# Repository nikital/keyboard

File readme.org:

#+STARTUP: indent

* Layout
Generated at http://www.keyboard-layout-editor.com/

* Plate
Generated at http://builder.swillkb.com/
- Switch Type: MX
- Stabilizer: Cherry Only

* PCB

** Placement
5.7mm 7.5mm For diodes from pin 1

** Components

*** MCU
ATMEGA32U4-AU

*** PPTC
MF-PSMF020X-2

*** I/O expander
MCP23018-E/SO

*** Resistors (2012/0805)

*** ESD protection
PRTR5V0U2X

* Burn
Load DFU bootloader. When using Arduino as ISP, first burn an Arduino using the
ArduinoISP example sketch. Then wire everything according to comments. Make sure
to use a good 5V source and the the 5V on ICSP (not sure why, but it glitched).
Then run:
#+begin_src sh
avrdude -patmega32u4 -cstk500v1 -P/dev/ttyUSB0 -b19200 -e -U flash:w:dfu/ATMega32U4-usbdevice_dfu-1_0_0.hex:i -U lfuse:w:0b01011110:m -U hfuse:w:0b10011001:m -U efuse:w:0b11000011:m -U lock:w:0b101100:m
#+end_src

If using a USBasp based programmer, use: =-cusbasp=.
#+begin_src sh
avrdude -patmega32u4 -cusbasp -e -U flash:w:dfu/ATMega32U4-usbdevice_dfu-1_0_0.hex:i -U lfuse:w:0b01011110:m -U hfuse:w:0b10011001:m -U efuse:w:0b11000011:m -U lock:w:0b101100:m
#+end_src

Make sure to issue an ~dfu-programmer atmega32u4 erase --force~ to make sure that the flash
is writable.

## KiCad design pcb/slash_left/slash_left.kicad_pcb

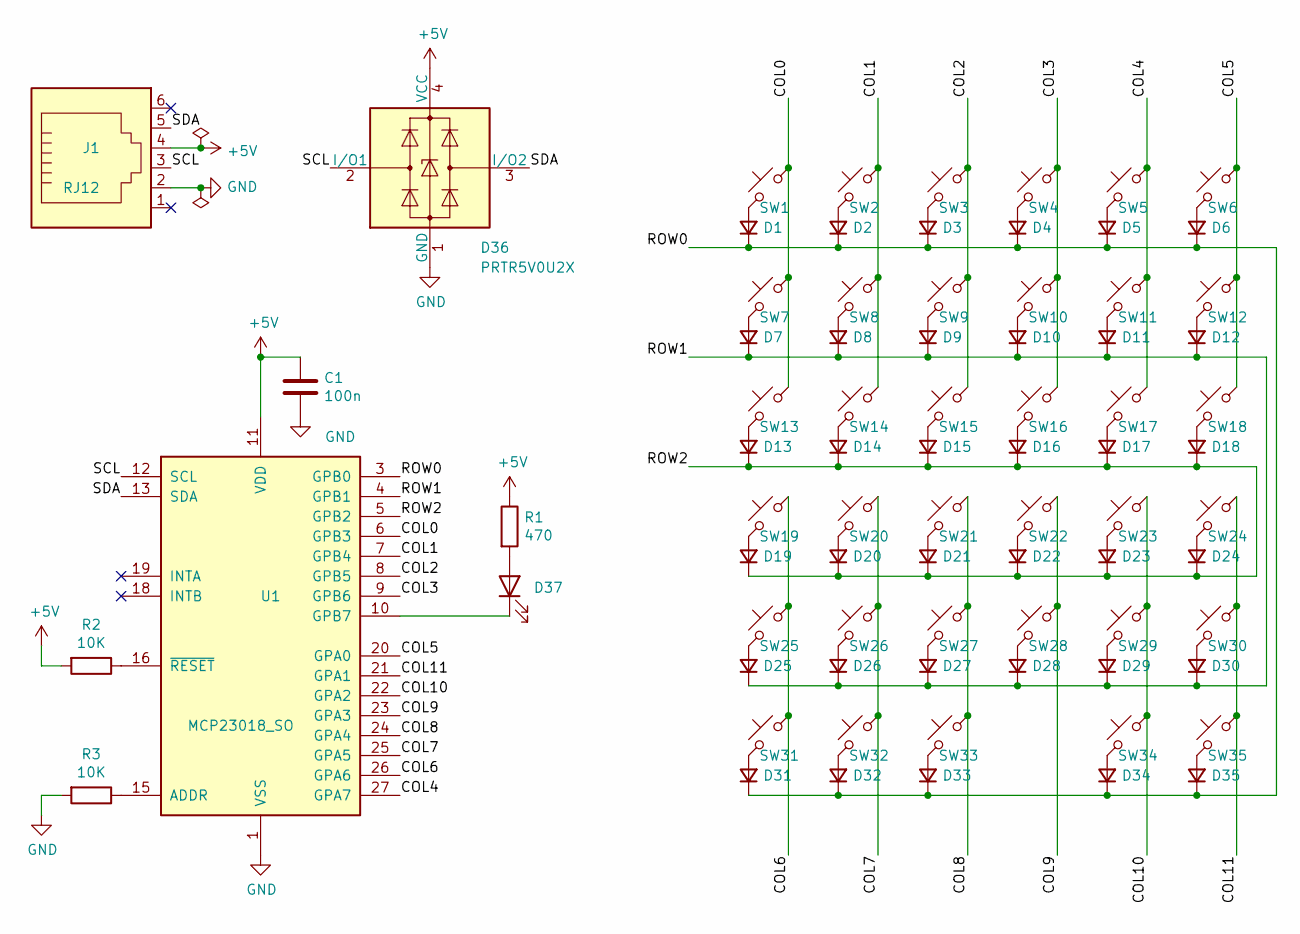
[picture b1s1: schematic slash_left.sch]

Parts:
C1: 100n; C_0805_2012Metric_Pad1.18x1.45mm_HandSolder
D1, D2, D3, D4, D5, D6, D7, D8, D9, D10, D11, D12, D13, D14, D15, D16, D17, D18, D19, D20, D21, D22, D23, D24, D25, D26, D27, D28, D29, D30, D31, D32, D33, D34, D35: D_Small; D_SOD-123
D36: PRTR5V0U2X; SOT-143
D37: LED; LED_0805_2012Metric_Pad1.15x1.40mm_HandSolder
J1: RJ12; RJ12_Custom1
R1: 470; R_0805_2012Metric_Pad1.20x1.40mm_HandSolder
R2, R3: 10K; R_0805_2012Metric_Pad1.20x1.40mm_HandSolder
SW1, SW2, SW3, SW4, SW5, SW6, SW7, SW8, SW9, SW10, SW11, SW12, SW13, SW14, SW15, SW16, SW17, SW18, SW19, SW20, SW21, SW22, SW23, SW24, SW25, SW26, SW27, SW28, SW29, SW30, SW31, SW32, SW33, SW34, SW35: SW_Push_45deg; Kailh_socket_MX
U1: MCP23018_SO; SOIC-28W_7.5x17.9mm_P1.27mm

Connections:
+5V: C1.1, D36.4 (VCC), J1.4, R1.1, R2.2, U1.11 (VDD)
/COL0: SW1.2, SW7.2, SW13.2, U1.6 (GPB3)
/COL1: SW2.2, SW8.2, SW14.2, U1.7 (GPB4)
/COL2: SW3.2, SW9.2, SW15.2, U1.8 (GPB5)
/COL3: SW4.2, SW10.2, SW16.2, U1.9 (GPB6)
/COL4: SW5.2, SW11.2, SW17.2, U1.27 (GPA7)
/COL5: SW6.2, SW12.2, SW18.2, U1.20 (GPA0)
/COL6: SW19.2, SW25.2, SW31.2, U1.26 (GPA6)
/COL7: SW20.2, SW26.2, SW32.2, U1.25 (GPA5)
/COL8: SW21.2, SW27.2, SW33.2, U1.24 (GPA4)
/COL9: SW22.2, SW28.2, U1.23 (GPA3)
/COL10: SW23.2, SW29.2, SW34.2, U1.22 (GPA2)
/COL11: SW24.2, SW30.2, SW35.2, U1.21 (GPA1)
/ROW0: D1.1 (K), D2.1 (K), D3.1 (K), D4.1 (K), D5.1 (K), D6.1 (K), D31.1 (K), D32.1 (K), D33.1 (K), D34.1 (K), D35.1 (K), U1.3 (GPB0)
/ROW1: D7.1 (K), D8.1 (K), D9.1 (K), D10.1 (K), D11.1 (K), D12.1 (K), D25.1 (K), D26.1 (K), D27.1 (K), D28.1 (K), D29.1 (K), D30.1 (K), U1.4 (GPB1)
/ROW2: D13.1 (K), D14.1 (K), D15.1 (K), D16.1 (K), D17.1 (K), D18.1 (K), D19.1 (K), D20.1 (K), D21.1 (K), D22.1 (K), D23.1 (K), D24.1 (K), U1.5 (GPB2)
/SCL: D36.2 (I/O1), J1.3, U1.12 (SCL)
/SDA: D36.3 (I/O2), J1.5, U1.13 (SDA)
GND: C1.2, D36.1 (GND), J1.2, R3.2, U1.1 (VSS)
unnamed: D1.2 (A), SW1.1
unnamed: D2.2 (A), SW2.1
unnamed: D3.2 (A), SW3.1
unnamed: D4.2 (A), SW4.1
unnamed: D5.2 (A), SW5.1
unnamed: D6.2 (A), SW6.1
unnamed: D7.2 (A), SW7.1
unnamed: D8.2 (A), SW8.1
unnamed: D9.2 (A), SW9.1
unnamed: D10.2 (A), SW10.1
unnamed: D11.2 (A), SW11.1
unnamed: D12.2 (A), SW12.1
unnamed: D13.2 (A), SW13.1
unnamed: D14.2 (A), SW14.1
unnamed: D15.2 (A), SW15.1
unnamed: D16.2 (A), SW16.1
unnamed: D17.2 (A), SW17.1
unnamed: D18.2 (A), SW18.1
unnamed: D19.2 (A), SW19.1
unnamed: D20.2 (A), SW20.1
unnamed: D21.2 (A), SW21.1
unnamed: D22.2 (A), SW22.1
unnamed: D23.2 (A), SW23.1
unnamed: D24.2 (A), SW24.1
unnamed: D25.2 (A), SW25.1
unnamed: D26.2 (A), SW26.1
unnamed: D27.2 (A), SW27.1
unnamed: D28.2 (A), SW28.1
unnamed: D29.2 (A), SW29.1
unnamed: D30.2 (A), SW30.1
unnamed: D31.2 (A), SW31.1
unnamed: D32.2 (A), SW32.1
unnamed: D33.2 (A), SW33.1
unnamed: D34.2 (A), SW34.1
unnamed: D35.2 (A), SW35.1
unnamed: D37.1 (K), U1.10 (GPB7)
unnamed: D37.2 (A), R1.2
unnamed: R2.1, U1.16 (~RESET)
unnamed: R3.1, U1.15 (ADDR)

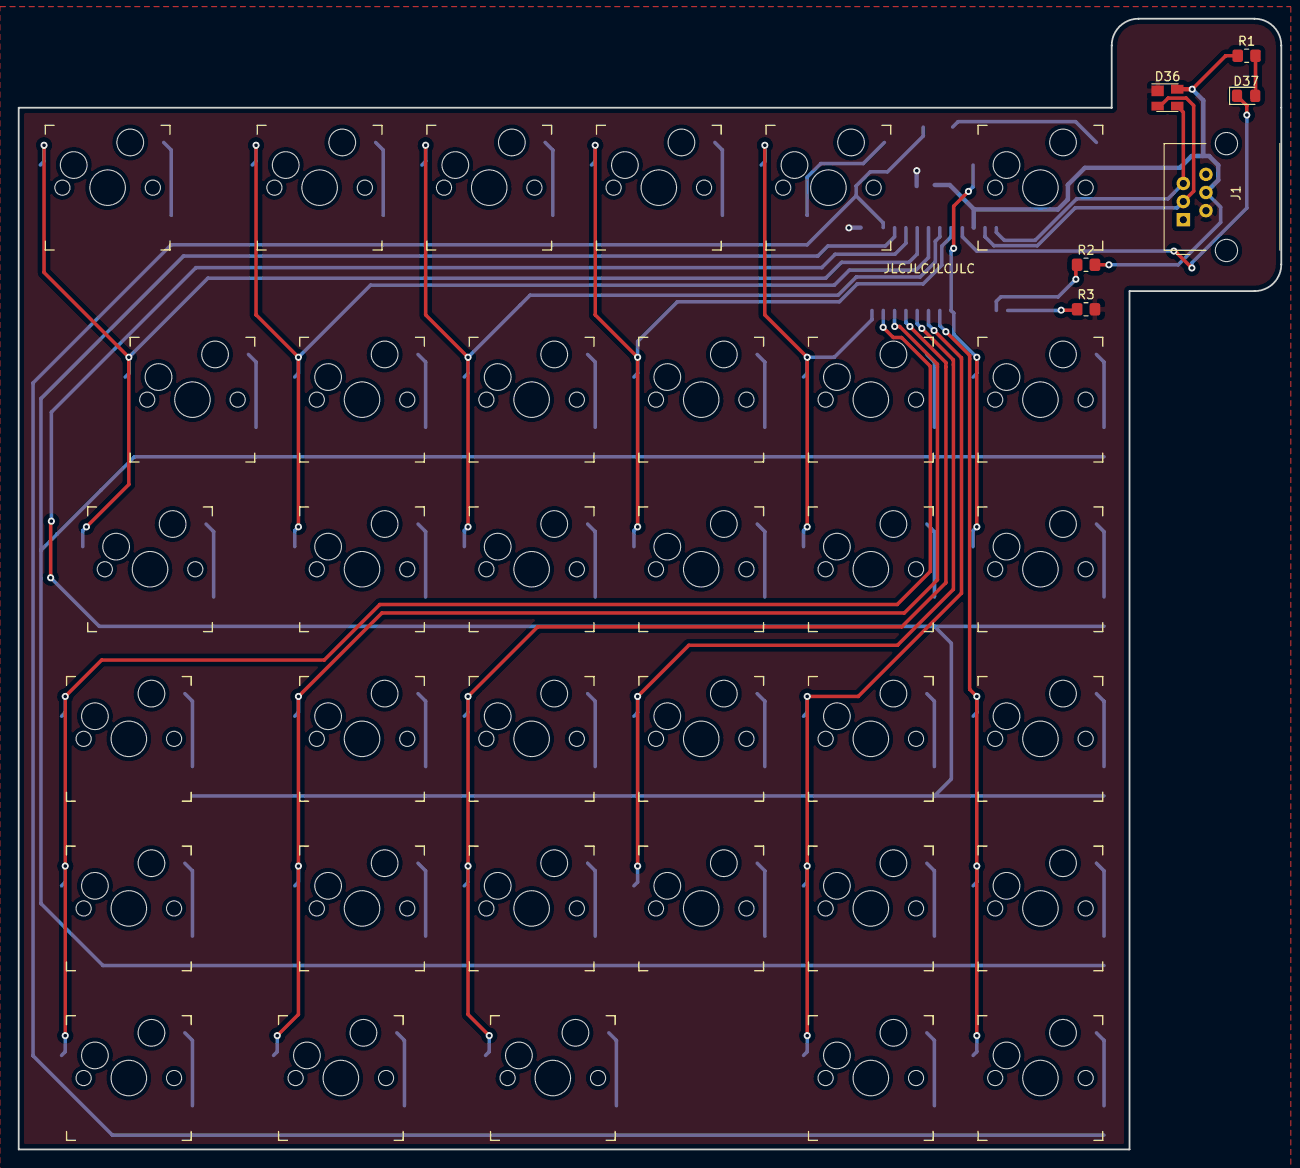
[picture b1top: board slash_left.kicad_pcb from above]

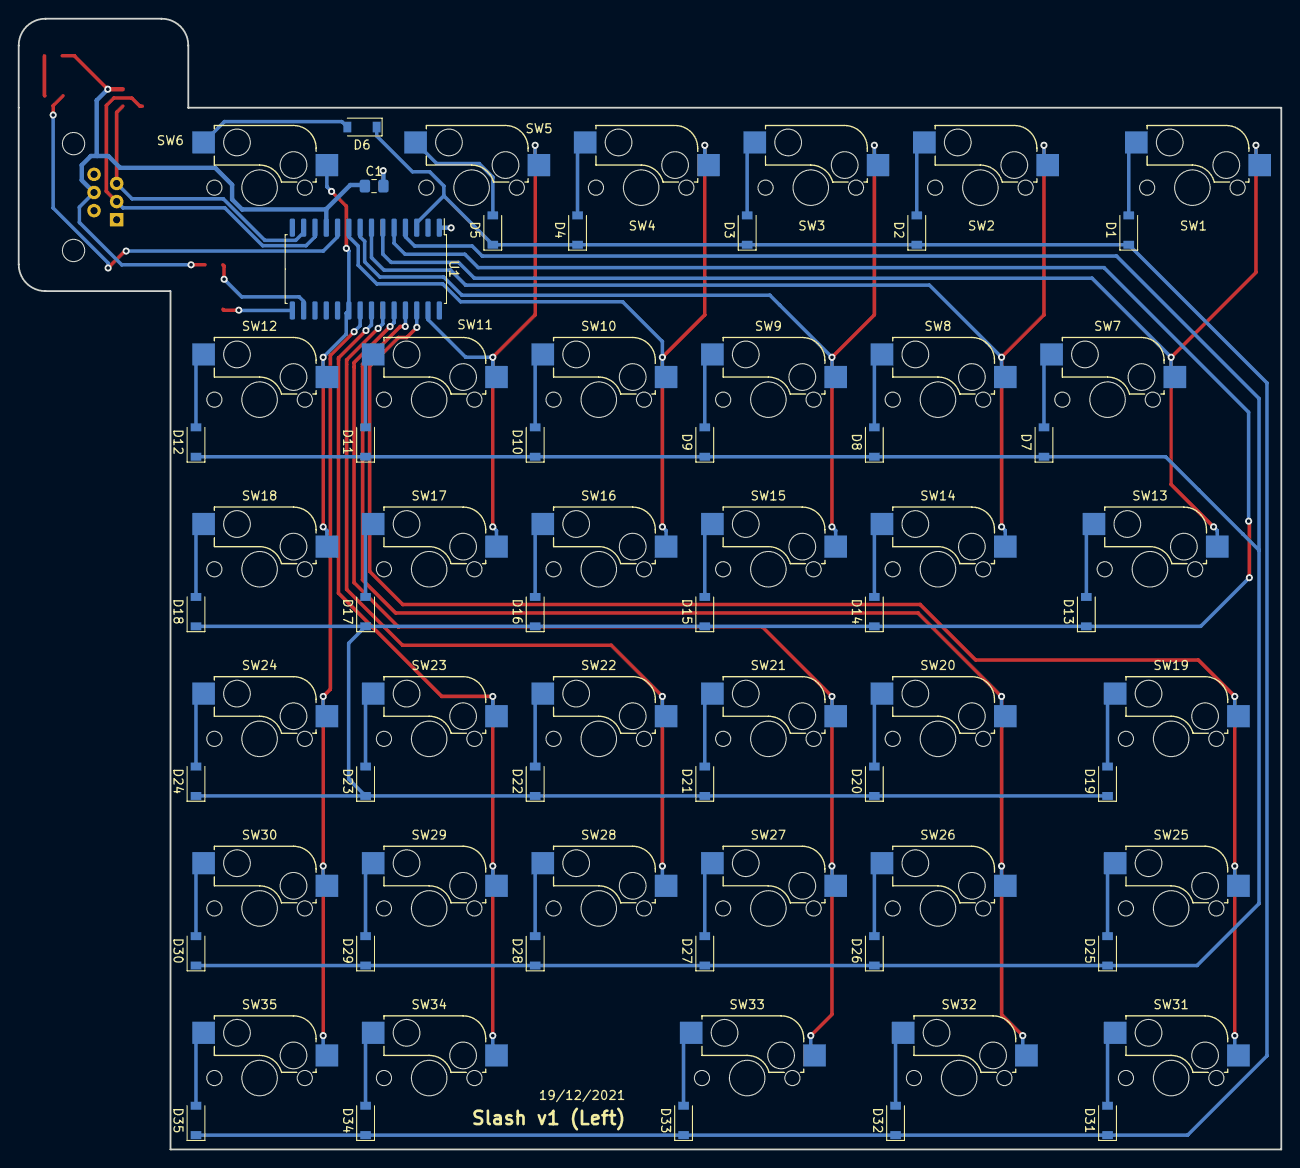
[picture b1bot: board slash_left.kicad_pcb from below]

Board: 2 copper layers, 141.8 x 127.0 mm, 78 parts (37 on the bottom side), 58 nets.

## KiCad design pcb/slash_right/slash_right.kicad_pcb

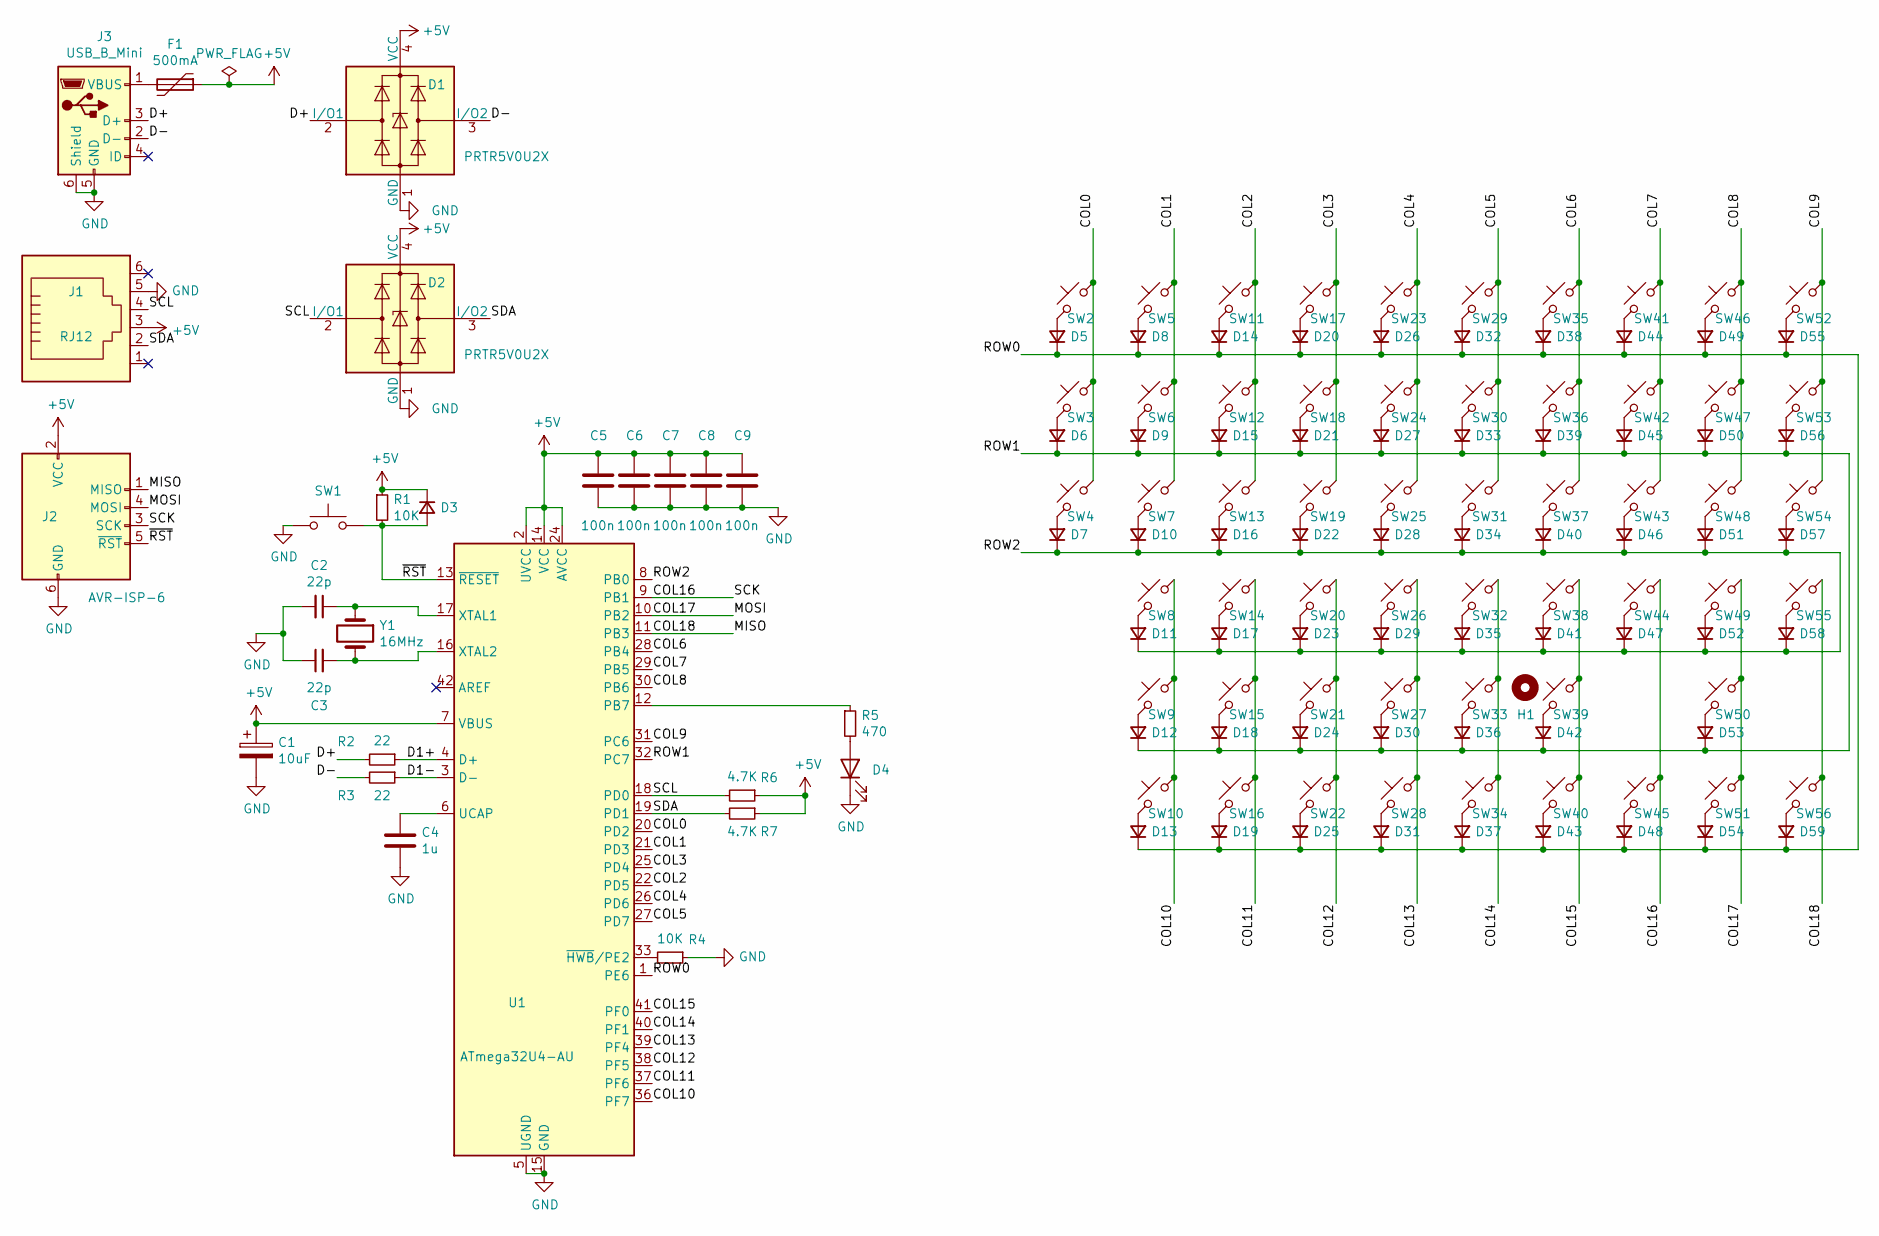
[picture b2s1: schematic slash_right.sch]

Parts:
C1: 10uF; CP_EIA-3216-18_Kemet-A_Pad1.58x1.35mm_HandSolder
C2, C3: 22p; C_0805_2012Metric_Pad1.18x1.45mm_HandSolder
C4: 1u; C_0805_2012Metric_Pad1.18x1.45mm_HandSolder
C5, C6, C7, C8, C9: 100n; C_0805_2012Metric_Pad1.18x1.45mm_HandSolder
D1, D2: PRTR5V0U2X; SOT-143
D3, D5, D6, D7, D8, D9, D10, D11, D12, D13, D14, D15, D16, D17, D18, D19, D20, D21, D22, D23, D24, D25, D26, D27, D28, D29, D30, D31, D32, D33, D34, D35, D36, D37, D38, D39, D40, D41, D42, D43, D44, D45, D46, D47, D48, D49, D50, D51, D52, D53, D54, D55, D56, D57, D58, D59: D_Small; D_SOD-123
D4: LED; LED_0805_2012Metric_Pad1.15x1.40mm_HandSolder
F1: 500mA; Fuse_0805_2012Metric_Pad1.15x1.40mm_HandSolder
H1: MountingHole; Stabilizer_MX_2u
J1: RJ12; RJ12_Custom1
J2: AVR-ISP-6; PinHeader_2x03_P2.54mm_Vertical
J3: USB_B_Mini; USB_Mini-B_Custom1_Horizontal
R1, R4: 10K; R_0805_2012Metric_Pad1.20x1.40mm_HandSolder
R2, R3: 22; R_0805_2012Metric_Pad1.20x1.40mm_HandSolder
R5: 470; R_0805_2012Metric_Pad1.20x1.40mm_HandSolder
R6, R7: 4.7K; R_0805_2012Metric_Pad1.20x1.40mm_HandSolder
SW1: SW_Push; SW_PUSH_6mm_H4.3mm
SW2, SW3, SW4, SW5, SW6, SW7, SW8, SW9, SW10, SW11, SW12, SW13, SW14, SW15, SW16, SW17, SW18, SW19, SW20, SW21, SW22, SW23, SW24, SW25, SW26, SW27, SW28, SW29, SW30, SW31, SW32, SW33, SW34, SW35, SW36, SW37, SW38, SW39, SW40, SW41, SW42, SW43, SW44, SW45, SW46, SW47, SW48, SW49, SW50, SW51, SW52, SW53, SW54, SW55, SW56: SW_Push_45deg; Kailh_socket_MX
U1: ATmega32U4-AU; TQFP-44_10x10mm_P0.8mm
Y1: 16MHz; Crystal_HC49-U_Vertical

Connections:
+5V: C1.1, C5.1, C6.1, C7.1, C8.1, C9.1, D1.4 (VCC), D2.4 (VCC), D3.1 (K), F1.1, J1.3, J2.2 (VCC), R1.1, R6.1, R7.1, U1.2 (UVCC), U1.7 (VBUS), U1.14 (VCC), U1.24 (AVCC), U1.34 (VCC), U1.44 (AVCC)
/COL0: SW2.2, SW3.2, SW4.2, U1.20 (PD2)
/COL1: SW5.2, SW6.2, SW7.2, U1.21 (PD3)
/COL2: SW11.2, SW12.2, SW13.2, U1.22 (PD5)
/COL3: SW17.2, SW18.2, SW19.2, U1.25 (PD4)
/COL4: SW23.2, SW24.2, SW25.2, U1.26 (PD6)
/COL5: SW29.2, SW30.2, SW31.2, U1.27 (PD7)
/COL6: SW35.2, SW36.2, SW37.2, U1.28 (PB4)
/COL7: SW41.2, SW42.2, SW43.2, U1.29 (PB5)
/COL8: SW46.2, SW47.2, SW48.2, U1.30 (PB6)
/COL9: SW52.2, SW53.2, SW54.2, U1.31 (PC6)
/COL10: SW8.2, SW9.2, SW10.2, U1.36 (PF7)
/COL11: SW14.2, SW15.2, SW16.2, U1.37 (PF6)
/COL12: SW20.2, SW21.2, SW22.2, U1.38 (PF5)
/COL13: SW26.2, SW27.2, SW28.2, U1.39 (PF4)
/COL14: SW32.2, SW33.2, SW34.2, U1.40 (PF1)
/COL15: SW38.2, SW39.2, SW40.2, U1.41 (PF0)
/COL16: J2.3 (SCK), SW44.2, SW45.2, U1.9 (PB1)
/COL17: J2.4 (MOSI), SW49.2, SW50.2, SW51.2, U1.10 (PB2)
/COL18: J2.1 (MISO), SW55.2, SW56.2, U1.11 (PB3)
/D1+: R2.1, U1.4 (D+)
/D1-: R3.1, U1.3 (D-)
/D+: D1.2 (I/O1), J3.3 (D+), R2.2
/D-: D1.3 (I/O2), J3.2 (D-), R3.2
/ROW0: D5.1 (K), D8.1 (K), D13.1 (K), D14.1 (K), D19.1 (K), D20.1 (K), D25.1 (K), D26.1 (K), D31.1 (K), D32.1 (K), D37.1 (K), D38.1 (K), D43.1 (K), D44.1 (K), D48.1 (K), D49.1 (K), D54.1 (K), D55.1 (K), D59.1 (K), U1.1 (PE6)
/ROW1: D6.1 (K), D9.1 (K), D12.1 (K), D15.1 (K), D18.1 (K), D21.1 (K), D24.1 (K), D27.1 (K), D30.1 (K), D33.1 (K), D36.1 (K), D39.1 (K), D42.1 (K), D45.1 (K), D50.1 (K), D53.1 (K), D56.1 (K), U1.32 (PC7)
/ROW2: D7.1 (K), D10.1 (K), D11.1 (K), D16.1 (K), D17.1 (K), D22.1 (K), D23.1 (K), D28.1 (K), D29.1 (K), D34.1 (K), D35.1 (K), D40.1 (K), D41.1 (K), D46.1 (K), D47.1 (K), D51.1 (K), D52.1 (K), D57.1 (K), D58.1 (K), U1.8 (PB0)
/SCL: D2.2 (I/O1), J1.4, R6.2, U1.18 (PD0)
/SDA: D2.3 (I/O2), J1.2, R7.2, U1.19 (PD1)
/~RST: D3.2 (A), J2.5 (~RST), R1.2, SW1.2, U1.13 (~RESET)
GND: C1.2, C2.2, C3.1, C4.2, C5.2, C6.2, C7.2, C8.2, C9.2, D1.1 (GND), D2.1 (GND), D4.1 (K), J1.5, J2.6 (GND), J3.5 (GND), J3.6 (Shield), R4.1, SW1.1, U1.5 (UGND), U1.15 (GND), U1.23 (GND), U1.35 (GND), U1.43 (GND)
unnamed: C2.1, U1.17 (XTAL1), Y1.1
unnamed: C3.2, U1.16 (XTAL2), Y1.2
unnamed: C4.1, U1.6 (UCAP)
unnamed: D4.2 (A), R5.2
unnamed: D5.2 (A), SW2.1
unnamed: D6.2 (A), SW3.1
unnamed: D7.2 (A), SW4.1
unnamed: D8.2 (A), SW5.1
unnamed: D9.2 (A), SW6.1
unnamed: D10.2 (A), SW7.1
unnamed: D11.2 (A), SW8.1
unnamed: D12.2 (A), SW9.1
unnamed: D13.2 (A), SW10.1
unnamed: D14.2 (A), SW11.1
unnamed: D15.2 (A), SW12.1
unnamed: D16.2 (A), SW13.1
unnamed: D17.2 (A), SW14.1
unnamed: D18.2 (A), SW15.1
unnamed: D19.2 (A), SW16.1
unnamed: D20.2 (A), SW17.1
unnamed: D21.2 (A), SW18.1
unnamed: D22.2 (A), SW19.1
unnamed: D23.2 (A), SW20.1
unnamed: D24.2 (A), SW21.1
unnamed: D25.2 (A), SW22.1
unnamed: D26.2 (A), SW23.1
unnamed: D27.2 (A), SW24.1
unnamed: D28.2 (A), SW25.1
unnamed: D29.2 (A), SW26.1
unnamed: D30.2 (A), SW27.1
unnamed: D31.2 (A), SW28.1
unnamed: D32.2 (A), SW29.1
unnamed: D33.2 (A), SW30.1
unnamed: D34.2 (A), SW31.1
unnamed: D35.2 (A), SW32.1
unnamed: D36.2 (A), SW33.1
unnamed: D37.2 (A), SW34.1
unnamed: D38.2 (A), SW35.1
unnamed: D39.2 (A), SW36.1
unnamed: D40.2 (A), SW37.1
unnamed: D41.2 (A), SW38.1
unnamed: D42.2 (A), SW39.1
unnamed: D43.2 (A), SW40.1
unnamed: D44.2 (A), SW41.1
unnamed: D45.2 (A), SW42.1
unnamed: D46.2 (A), SW43.1
unnamed: D47.2 (A), SW44.1
unnamed: D48.2 (A), SW45.1
unnamed: D49.2 (A), SW46.1
unnamed: D50.2 (A), SW47.1
unnamed: D51.2 (A), SW48.1
unnamed: D52.2 (A), SW49.1
unnamed: D53.2 (A), SW50.1
unnamed: D54.2 (A), SW51.1
unnamed: D55.2 (A), SW52.1
unnamed: D56.2 (A), SW53.1
unnamed: D57.2 (A), SW54.1
unnamed: D58.2 (A), SW55.1
unnamed: D59.2 (A), SW56.1
unnamed: F1.2, J3.1 (VBUS)
unnamed: R4.2, U1.33 (~HWB~/PE2)
unnamed: R5.1, U1.12 (PB7)

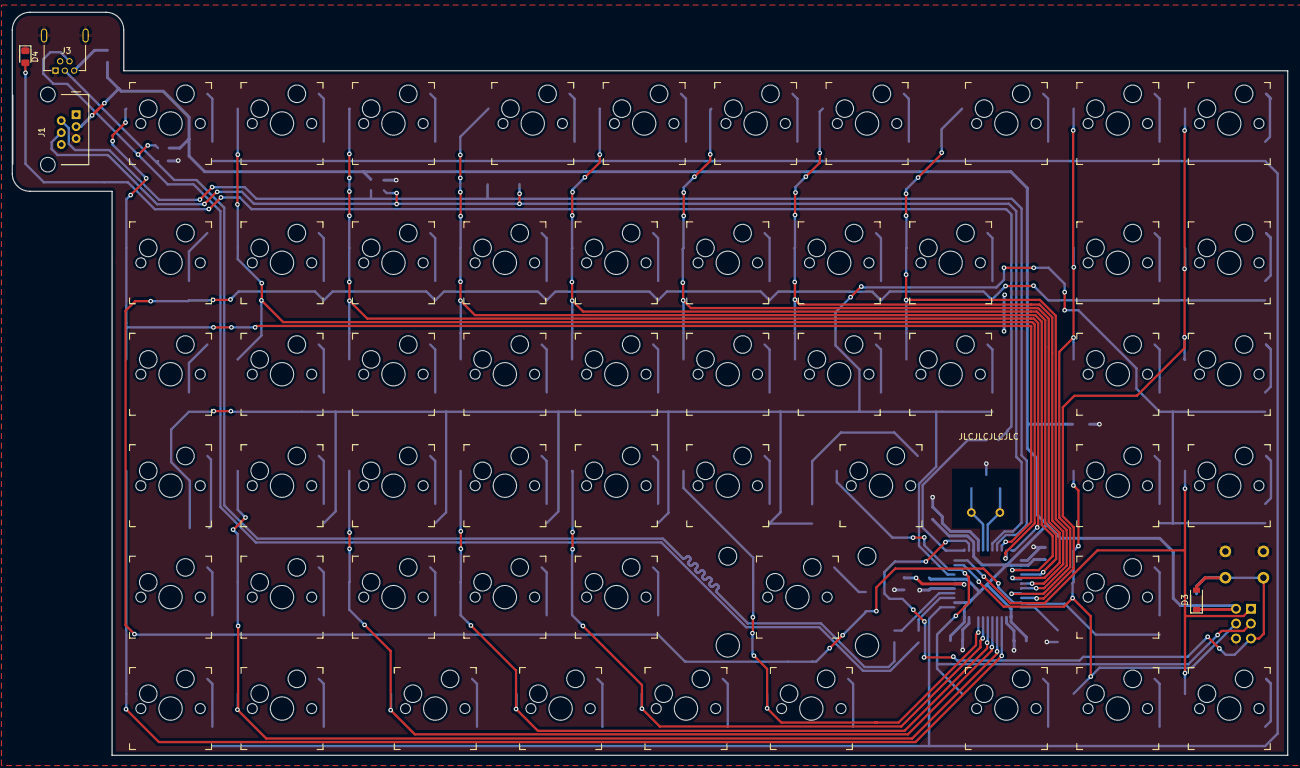
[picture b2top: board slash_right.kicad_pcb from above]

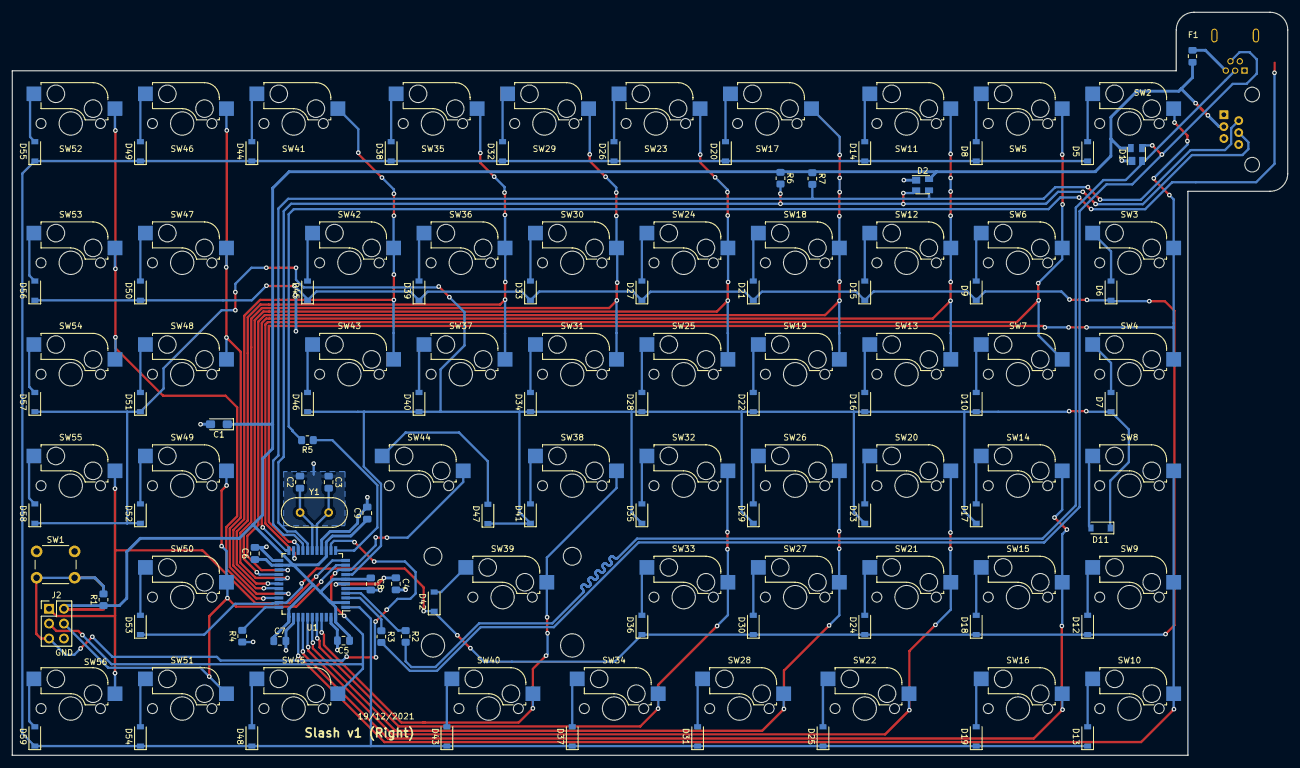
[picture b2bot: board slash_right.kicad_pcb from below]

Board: 2 copper layers, 218.0 x 127.0 mm, 138 parts (78 on the bottom side), 93 nets.

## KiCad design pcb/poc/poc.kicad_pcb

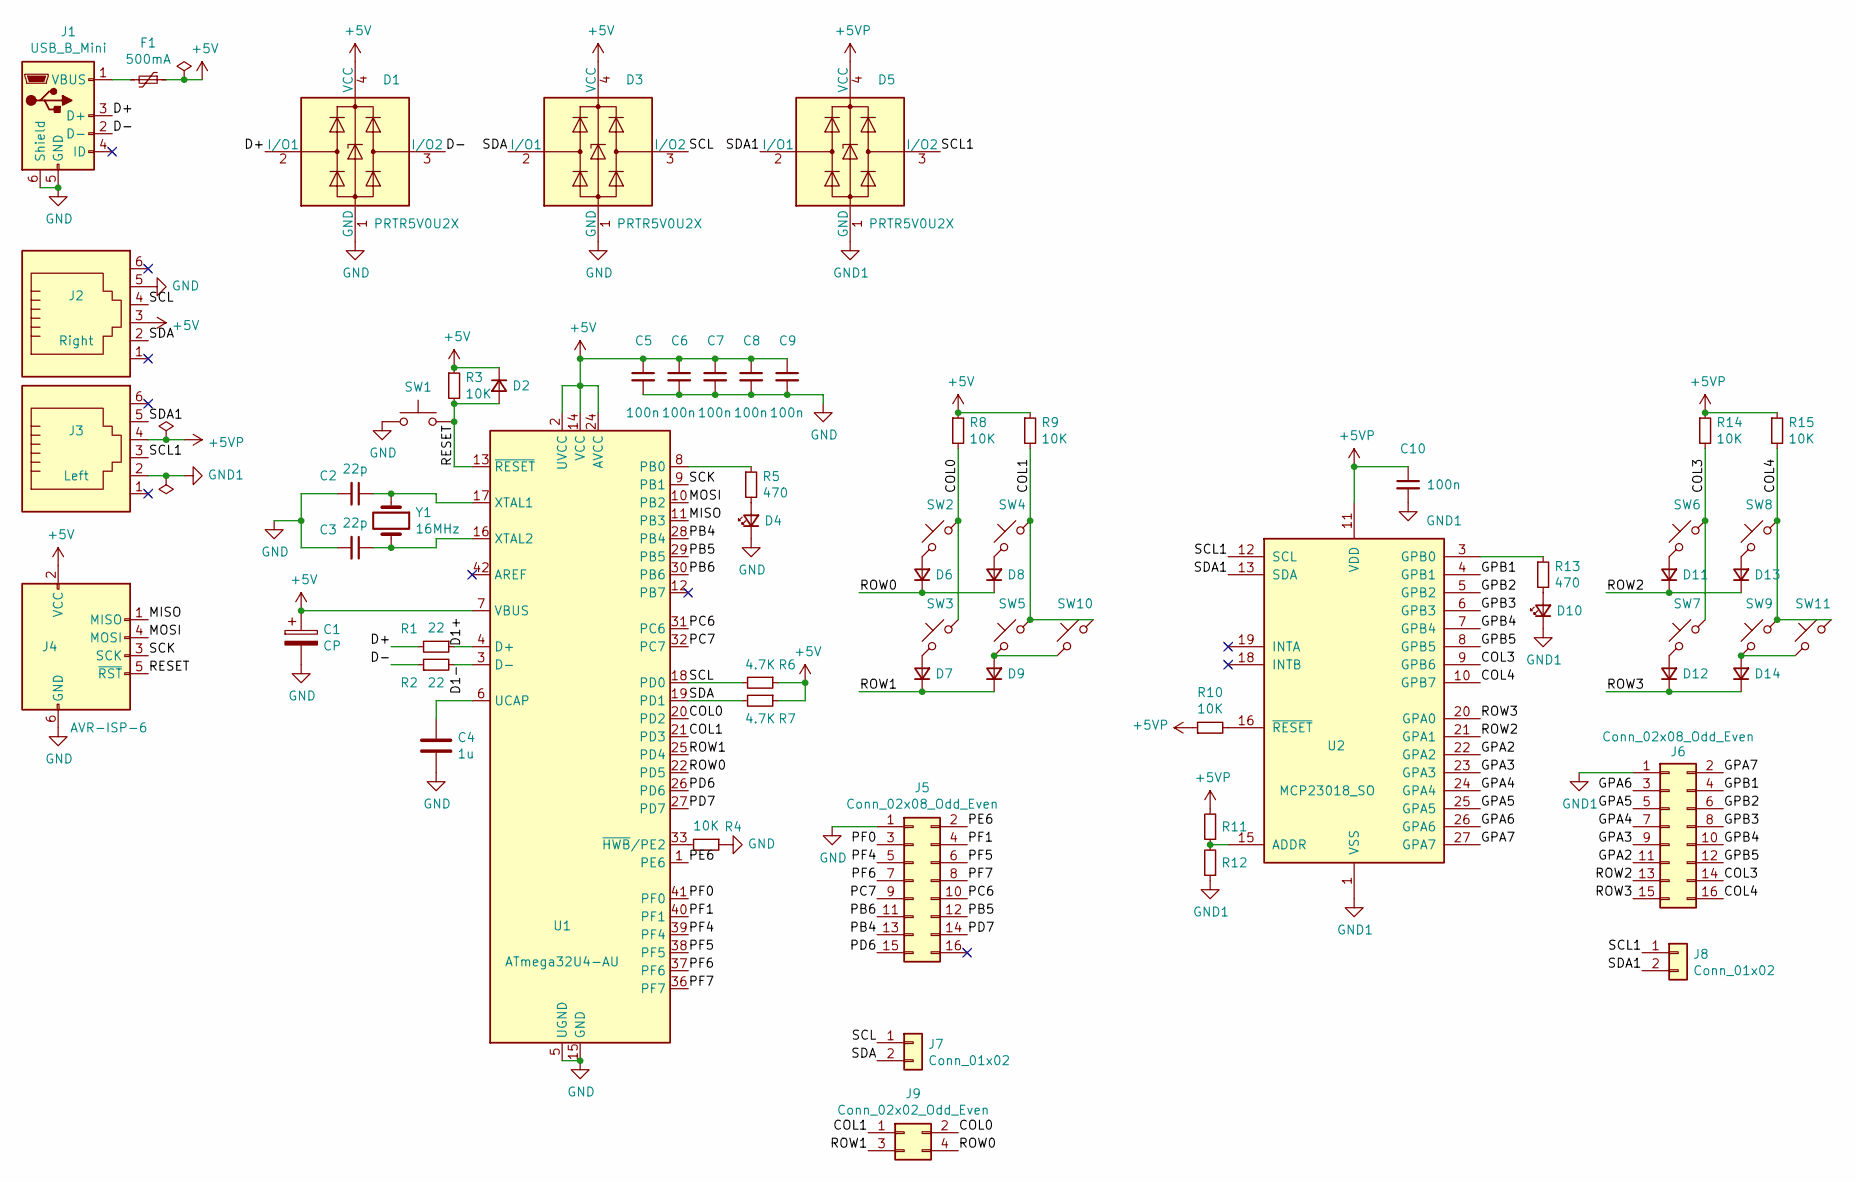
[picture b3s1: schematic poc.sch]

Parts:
C1: CP; CP_EIA-3216-18_Kemet-A_Pad1.58x1.35mm_HandSolder
C2, C3: 22p; C_0805_2012Metric_Pad1.18x1.45mm_HandSolder
C4: 1u; C_0805_2012Metric_Pad1.18x1.45mm_HandSolder
C5, C6, C7, C8, C9, C10: 100n; C_0805_2012Metric_Pad1.18x1.45mm_HandSolder
D1, D3, D5: PRTR5V0U2X; SOT-143
D2, D6, D7, D8, D9, D11, D12, D13, D14: D_Small; D_SOD-123
D4, D10: LED_Small; LED_0805_2012Metric_Pad1.15x1.40mm_HandSolder
F1: 500mA; Fuse_0805_2012Metric_Pad1.15x1.40mm_HandSolder
J1: USB_B_Mini; USB_Mini-B_Custom1_Horizontal
J2: Right; RJ12_Custom1
J3: Left; RJ12_Custom1
J4: AVR-ISP-6; PinHeader_2x03_P2.54mm_Vertical
J5: Conn_02x08_Odd_Even; PinSocket_2x08_P2.54mm_Vertical
J6: Conn_02x08_Odd_Even; PinHeader_2x08_P2.54mm_Vertical
J7, J8: Conn_01x02; PinHeader_1x02_P2.54mm_Vertical
J9: Conn_02x02_Odd_Even; PinSocket_2x02_P2.54mm_Vertical
R1, R2: 22; R_0805_2012Metric_Pad1.20x1.40mm_HandSolder
R3, R4, R8, R9, R10, R14, R15: 10K; R_0805_2012Metric_Pad1.20x1.40mm_HandSolder
R5, R13: 470; R_0805_2012Metric_Pad1.20x1.40mm_HandSolder
R6, R7: 4.7K; R_0805_2012Metric_Pad1.20x1.40mm_HandSolder
R11, R12: R_Small; R_0805_2012Metric_Pad1.20x1.40mm_HandSolder
SW1: SW_Push; SW_PUSH_6mm_H4.3mm
SW2, SW3, SW4, SW5, SW6, SW7, SW8, SW9: SW_Push_45deg; SW_PUSH_6mm_H4.3mm
SW10, SW11: SW_Push_45deg; SW_Cherry_MX_1.00u_PCB
U1: ATmega32U4-AU; TQFP-44_10x10mm_P0.8mm
U2: MCP23018_SO; SOIC-28W_7.5x17.9mm_P1.27mm
Y1: 16MHz; Crystal_HC49-U_Vertical

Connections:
+5V: C1.1, C5.1, C6.1, C7.1, C8.1, C9.1, D1.4 (VCC), D2.1 (K), D3.4 (VCC), F1.1, J2.3, J4.2 (VCC), R3.1, R6.1, R7.1, R8.1, R9.1, U1.2 (UVCC), U1.7 (VBUS), U1.14 (VCC), U1.24 (AVCC), U1.34 (VCC), U1.44 (AVCC)
+5VP: C10.1, D5.4 (VCC), J3.4, R10.1, R11.2, R14.1, R15.1, U2.11 (VDD)
/COL0: J9.2, R8.2, SW2.1, SW3.1, U1.20 (PD2)
/COL1: J9.1, R9.2, SW4.1, SW5.1, SW10.1, U1.21 (PD3)
/COL3: J6.14, R14.2, SW6.1, SW7.1, U2.9 (GPB6)
/COL4: J6.16, R15.2, SW8.1, SW9.1, SW11.1, U2.10 (GPB7)
/D1+: R1.1, U1.4 (D+)
/D1-: R2.2, U1.3 (D-)
/D+: D1.2 (I/O1), J1.3 (D+), R1.2
/D-: D1.3 (I/O2), J1.2 (D-), R2.1
/GPA2: J6.11, U2.22 (GPA2)
/GPA3: J6.9, U2.23 (GPA3)
/GPA4: J6.7, U2.24 (GPA4)
/GPA5: J6.5, U2.25 (GPA5)
/GPA6: J6.3, U2.26 (GPA6)
/GPA7: J6.2, U2.27 (GPA7)
/GPB1: J6.4, U2.4 (GPB1)
/GPB2: J6.6, U2.5 (GPB2)
/GPB3: J6.8, U2.6 (GPB3)
/GPB4: J6.10, U2.7 (GPB4)
/GPB5: J6.12, U2.8 (GPB5)
/MISO: J4.1 (MISO), U1.11 (PB3)
/MOSI: J4.4 (MOSI), U1.10 (PB2)
/PB4: J5.13, U1.28 (PB4)
/PB5: J5.12, U1.29 (PB5)
/PB6: J5.11, U1.30 (PB6)
/PC6: J5.10, U1.31 (PC6)
/PC7: J5.9, U1.32 (PC7)
/PD6: J5.15, U1.26 (PD6)
/PD7: J5.14, U1.27 (PD7)
/PE6: J5.2, U1.1 (PE6)
/PF0: J5.3, U1.41 (PF0)
/PF1: J5.4, U1.40 (PF1)
/PF4: J5.5, U1.39 (PF4)
/PF5: J5.6, U1.38 (PF5)
/PF6: J5.7, U1.37 (PF6)
/PF7: J5.8, U1.36 (PF7)
/RESET: D2.2 (A), J4.5 (~RST), R3.2, SW1.2, U1.13 (~RESET)
/ROW0: D6.1 (K), D8.1 (K), J9.4, U1.22 (PD5)
/ROW1: D7.1 (K), D9.1 (K), J9.3, U1.25 (PD4)
/ROW2: D11.1 (K), D13.1 (K), J6.13, U2.21 (GPA1)
/ROW3: D12.1 (K), D14.1 (K), J6.15, U2.20 (GPA0)
/SCK: J4.3 (SCK), U1.9 (PB1)
/SCL: D3.3 (I/O2), J2.4, J7.1, R6.2, U1.18 (PD0)
/SCL1: D5.3 (I/O2), J3.3, J8.1, U2.12 (SCL)
/SDA: D3.2 (I/O1), J2.2, J7.2, R7.2, U1.19 (PD1)
/SDA1: D5.2 (I/O1), J3.5, J8.2, U2.13 (SDA)
GND: C1.2, C2.2, C3.2, C4.2, C5.2, C6.2, C7.2, C8.2, C9.2, D1.1 (GND), D3.1 (GND), D4.1 (K), J1.5 (GND), J1.6 (Shield), J2.5, J4.6 (GND), J5.1, R4.1, SW1.1, U1.5 (UGND), U1.15 (GND), U1.23 (GND), U1.35 (GND), U1.43 (GND)
GND1: C10.2, D5.1 (GND), D10.1 (K), J3.2, J6.1, R12.1, U2.1 (VSS)
unnamed: C2.1, U1.17 (XTAL1), Y1.1
unnamed: C3.1, U1.16 (XTAL2), Y1.2
unnamed: C4.1, U1.6 (UCAP)
unnamed: D4.2 (A), R5.2
unnamed: D6.2 (A), SW2.2
unnamed: D7.2 (A), SW3.2
unnamed: D8.2 (A), SW4.2
unnamed: D9.2 (A), SW5.2, SW10.2
unnamed: D10.2 (A), R13.2
unnamed: D11.2 (A), SW6.2
unnamed: D12.2 (A), SW7.2
unnamed: D13.2 (A), SW8.2
unnamed: D14.2 (A), SW9.2, SW11.2
unnamed: F1.2, J1.1 (VBUS)
unnamed: R4.2, U1.33 (~HWB~/PE2)
unnamed: R5.1, U1.8 (PB0)
unnamed: R10.2, U2.16 (~RESET)
unnamed: R11.1, R12.2, U2.15 (ADDR)
unnamed: R13.1, U2.3 (GPB0)

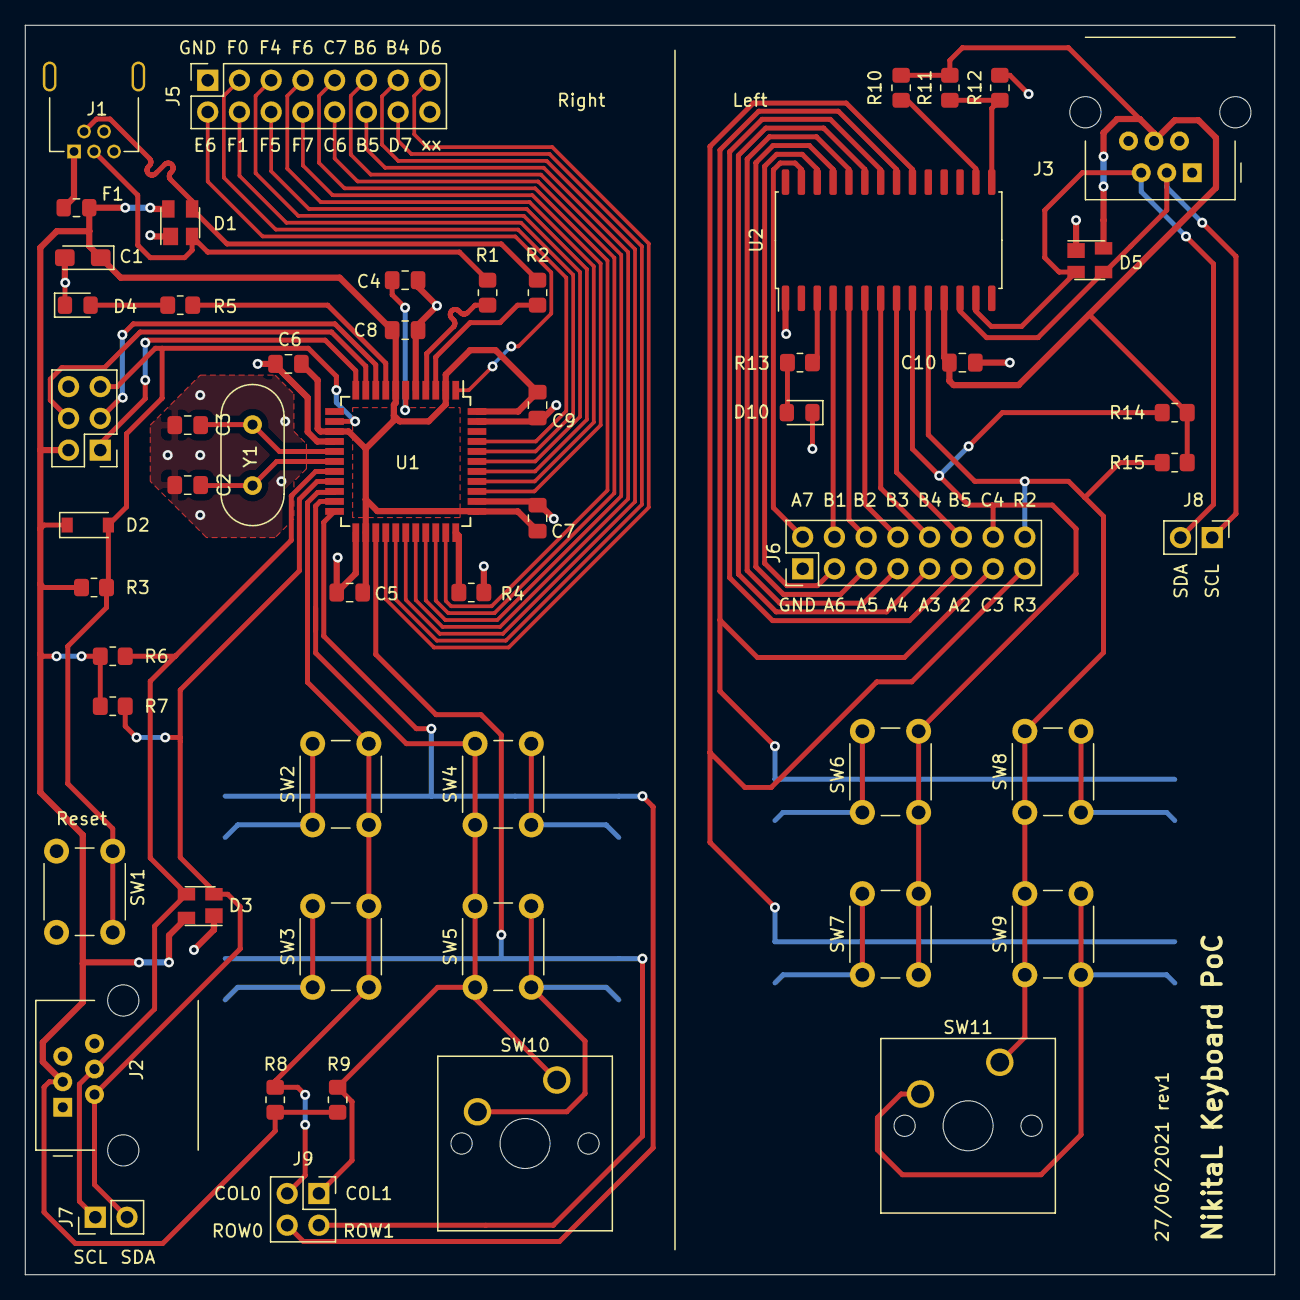
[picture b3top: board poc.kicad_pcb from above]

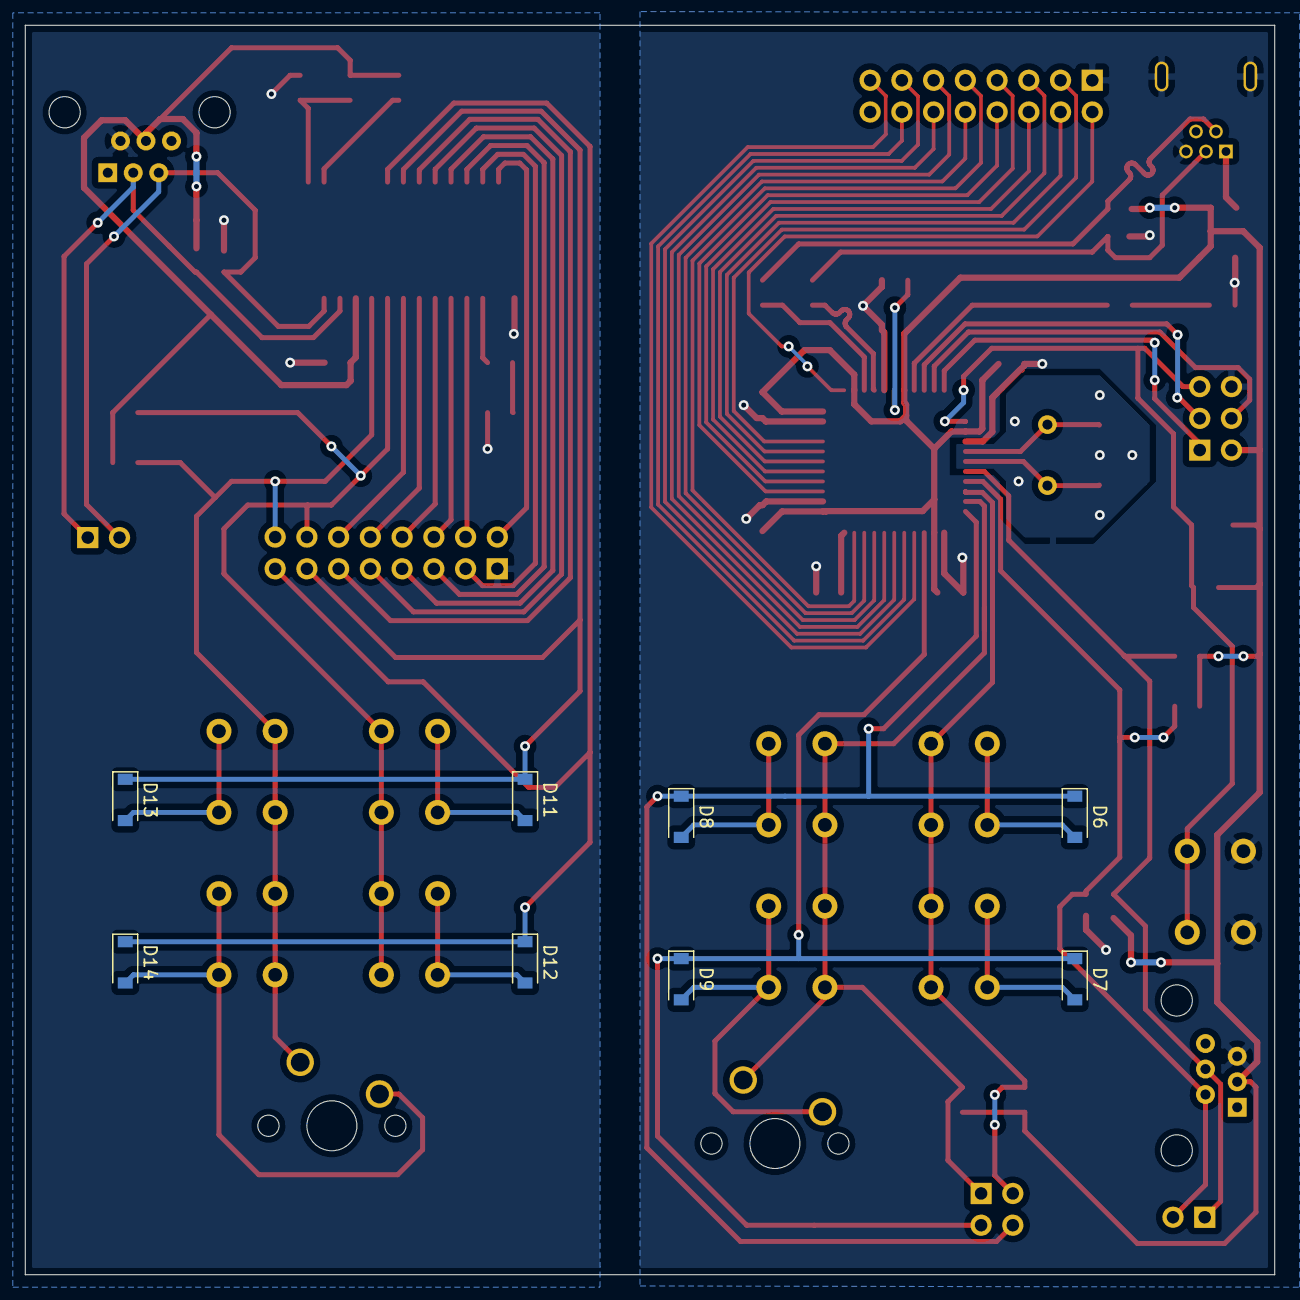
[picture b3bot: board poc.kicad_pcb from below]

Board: 2 copper layers, 100.0 x 100.0 mm, 63 parts (8 on the bottom side), 68 nets.
